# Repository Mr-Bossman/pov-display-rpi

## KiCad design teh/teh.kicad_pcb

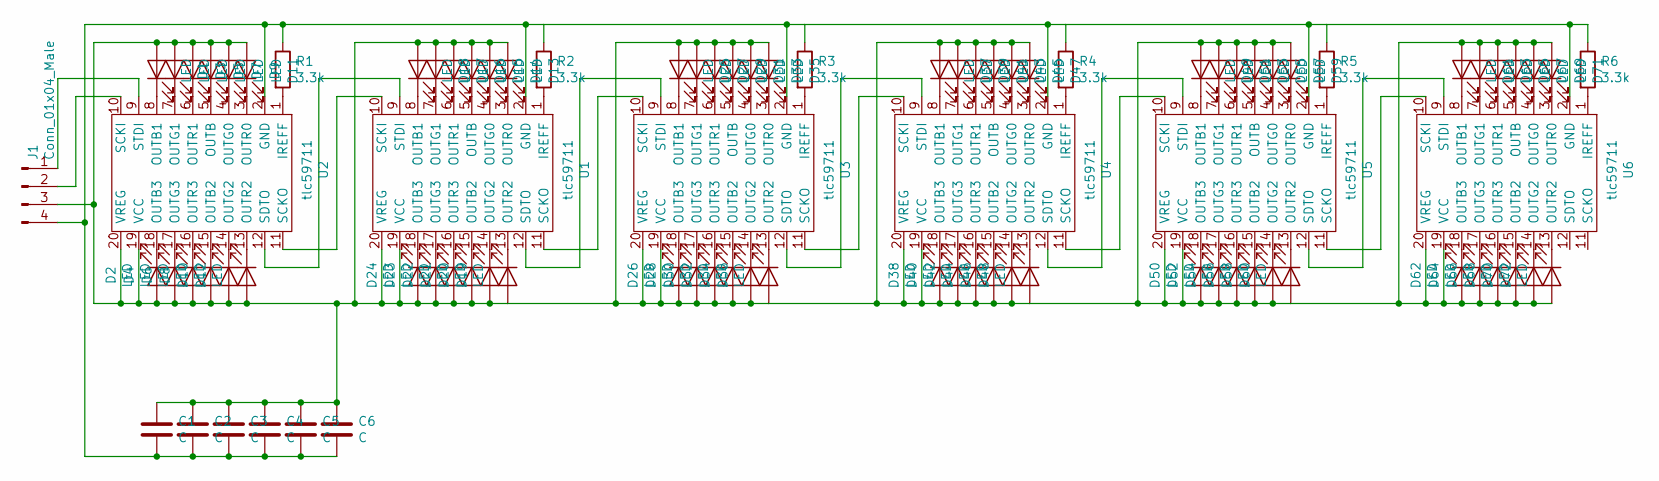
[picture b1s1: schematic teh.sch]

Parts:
C1, C2, C3, C4, C5, C6: C; C_0603_1608Metric
D1, D2, D3, D4, D5, D6, D7, D8, D9, D10, D11, D12, D13, D14, D15, D16, D17, D18, D19, D20, D21, D22, D23, D24, D25, D26, D27, D28, D29, D30, D31, D32, D33, D34, D35, D36, D37, D38, D39, D40, D41, D42, D43, D44, D45, D46, D47, D48, D49, D50, D51, D52, D53, D54, D55, D56, D57, D58, D59, D60, D61, D62, D63, D64, D65, D66, D67, D68, D69, D70, D71, D72: LED; LED_0603_1608Metric
J1: Conn_01x04_Male; PinSocket_1x04_P2.54mm_Vertical
R1, R2, R3, R4, R5, R6: 3.3k; R_0603_1608Metric
U1, U2, U3, U4, U5, U6: tlc59711; ETSSOP-20-1EP_4.4x6.5mm_P0.65mm_EP3x4.2mm_termal

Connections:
GND: C1.2, C2.2, C3.2, C4.2, C5.2, C6.2, J1.4, R1.1, R2.1, R3.1, R4.1, R5.1, R6.1, U1.2 (GND), U1.21 (GND), U2.2 (GND), U2.21 (GND), U3.2 (GND), U3.21 (GND), U4.2 (GND), U4.21 (GND), U5.2 (GND), U5.21 (GND), U6.2 (GND), U6.21 (GND)
unnamed: C1.1, C2.1, C3.1, C4.1, C5.1, C6.1, D1.2 (A), D2.2 (A), D3.2 (A), D4.2 (A), D5.2 (A), D6.2 (A), D7.2 (A), D8.2 (A), D9.2 (A), D10.2 (A), D11.2 (A), D12.2 (A), D13.2 (A), D14.2 (A), D15.2 (A), D16.2 (A), D17.2 (A), D18.2 (A), D19.2 (A), D20.2 (A), D21.2 (A), D22.2 (A), D23.2 (A), D24.2 (A), D25.2 (A), D26.2 (A), D27.2 (A), D28.2 (A), D29.2 (A), D30.2 (A), D31.2 (A), D32.2 (A), D33.2 (A), D34.2 (A), D35.2 (A), D36.2 (A), D37.2 (A), D38.2 (A), D39.2 (A), D40.2 (A), D41.2 (A), D42.2 (A), D43.2 (A), D44.2 (A), D45.2 (A), D46.2 (A), D47.2 (A), D48.2 (A), D49.2 (A), D50.2 (A), D51.2 (A), D52.2 (A), D53.2 (A), D54.2 (A), D55.2 (A), D56.2 (A), D57.2 (A), D58.2 (A), D59.2 (A), D60.2 (A), D61.2 (A), D62.2 (A), D63.2 (A), D64.2 (A), D65.2 (A), D66.2 (A), D67.2 (A), D68.2 (A), D69.2 (A), D70.2 (A), D71.2 (A), D72.2 (A), J1.3, U1.19 (VCC), U1.20 (VREG), U2.19 (VCC), U2.20 (VREG), U3.19 (VCC), U3.20 (VREG), U4.19 (VCC), U4.20 (VREG), U5.19 (VCC), U5.20 (VREG), U6.19 (VCC), U6.20 (VREG)
unnamed: D1.1 (K), U2.8 (OUTB1)
unnamed: D2.1 (K), U2.18 (OUTB3)
unnamed: D3.1 (K), U2.7 (OUTG1)
unnamed: D4.1 (K), U2.17 (OUTG3)
unnamed: D5.1 (K), U2.6 (OUTR1)
unnamed: D6.1 (K), U2.16 (OUTR3)
unnamed: D7.1 (K), U2.5 (OUTB)
unnamed: D8.1 (K), U2.15 (OUTB2)
unnamed: D9.1 (K), U2.4 (OUTG0)
unnamed: D10.1 (K), U2.14 (OUTG2)
unnamed: D11.1 (K), U2.3 (OUTR0)
unnamed: D12.1 (K), U2.13 (OUTR2)
unnamed: D13.1 (K), U1.3 (OUTR0)
unnamed: D14.1 (K), U1.4 (OUTG0)
unnamed: D15.1 (K), U1.5 (OUTB)
unnamed: D16.1 (K), U1.6 (OUTR1)
unnamed: D17.1 (K), U1.7 (OUTG1)
unnamed: D18.1 (K), U1.8 (OUTB1)
unnamed: D19.1 (K), U1.13 (OUTR2)
unnamed: D20.1 (K), U1.14 (OUTG2)
unnamed: D21.1 (K), U1.15 (OUTB2)
unnamed: D22.1 (K), U1.16 (OUTR3)
unnamed: D23.1 (K), U1.17 (OUTG3)
unnamed: D24.1 (K), U1.18 (OUTB3)
unnamed: D25.1 (K), U3.8 (OUTB1)
unnamed: D26.1 (K), U3.18 (OUTB3)
unnamed: D27.1 (K), U3.7 (OUTG1)
unnamed: D28.1 (K), U3.17 (OUTG3)
unnamed: D29.1 (K), U3.6 (OUTR1)
unnamed: D30.1 (K), U3.16 (OUTR3)
unnamed: D31.1 (K), U3.5 (OUTB)
unnamed: D32.1 (K), U3.15 (OUTB2)
unnamed: D33.1 (K), U3.4 (OUTG0)
unnamed: D34.1 (K), U3.14 (OUTG2)
unnamed: D35.1 (K), U3.3 (OUTR0)
unnamed: D36.1 (K), U3.13 (OUTR2)
unnamed: D37.1 (K), U4.8 (OUTB1)
unnamed: D38.1 (K), U4.18 (OUTB3)
unnamed: D39.1 (K), U4.7 (OUTG1)
unnamed: D40.1 (K), U4.17 (OUTG3)
unnamed: D41.1 (K), U4.6 (OUTR1)
unnamed: D42.1 (K), U4.16 (OUTR3)
unnamed: D43.1 (K), U4.5 (OUTB)
unnamed: D44.1 (K), U4.15 (OUTB2)
unnamed: D45.1 (K), U4.4 (OUTG0)
unnamed: D46.1 (K), U4.14 (OUTG2)
unnamed: D47.1 (K), U4.3 (OUTR0)
unnamed: D48.1 (K), U4.13 (OUTR2)
unnamed: D49.1 (K), U5.8 (OUTB1)
unnamed: D50.1 (K), U5.18 (OUTB3)
unnamed: D51.1 (K), U5.7 (OUTG1)
unnamed: D52.1 (K), U5.17 (OUTG3)
unnamed: D53.1 (K), U5.6 (OUTR1)
unnamed: D54.1 (K), U5.16 (OUTR3)
unnamed: D55.1 (K), U5.5 (OUTB)
unnamed: D56.1 (K), U5.15 (OUTB2)
unnamed: D57.1 (K), U5.4 (OUTG0)
unnamed: D58.1 (K), U5.14 (OUTG2)
unnamed: D59.1 (K), U5.3 (OUTR0)
unnamed: D60.1 (K), U5.13 (OUTR2)
unnamed: D61.1 (K), U6.8 (OUTB1)
unnamed: D62.1 (K), U6.18 (OUTB3)
unnamed: D63.1 (K), U6.7 (OUTG1)
unnamed: D64.1 (K), U6.17 (OUTG3)
unnamed: D65.1 (K), U6.6 (OUTR1)
unnamed: D66.1 (K), U6.16 (OUTR3)
unnamed: D67.1 (K), U6.5 (OUTB)
unnamed: D68.1 (K), U6.15 (OUTB2)
unnamed: D69.1 (K), U6.4 (OUTG0)
unnamed: D70.1 (K), U6.14 (OUTG2)
unnamed: D71.1 (K), U6.3 (OUTR0)
unnamed: D72.1 (K), U6.13 (OUTR2)
unnamed: J1.1, U2.9 (STDI)
unnamed: J1.2, U2.10 (SCKI)
unnamed: R1.2, U2.1 (IREFF)
unnamed: R2.2, U1.1 (IREFF)
unnamed: R3.2, U3.1 (IREFF)
unnamed: R4.2, U4.1 (IREFF)
unnamed: R5.2, U5.1 (IREFF)
unnamed: R6.2, U6.1 (IREFF)
unnamed: U1.9 (STDI), U2.12 (SDTO)
unnamed: U1.10 (SCKI), U2.11 (SCKO)
unnamed: U1.11 (SCKO), U3.10 (SCKI)
unnamed: U1.12 (SDTO), U3.9 (STDI)
unnamed: U3.11 (SCKO), U4.10 (SCKI)
unnamed: U3.12 (SDTO), U4.9 (STDI)
unnamed: U4.11 (SCKO), U5.10 (SCKI)
unnamed: U4.12 (SDTO), U5.9 (STDI)
unnamed: U5.11 (SCKO), U6.10 (SCKI)
unnamed: U5.12 (SDTO), U6.9 (STDI)

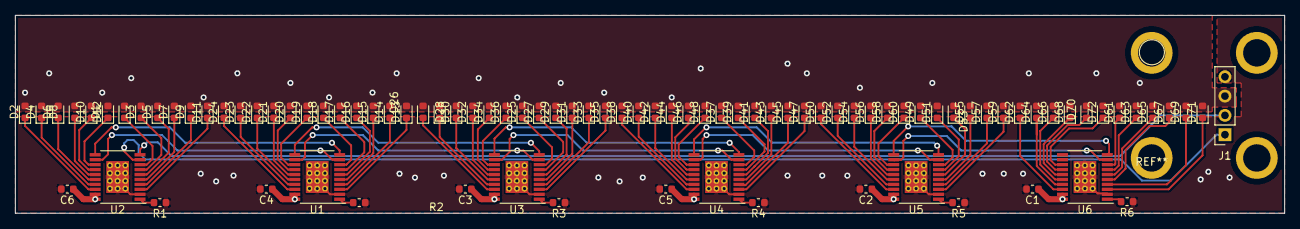
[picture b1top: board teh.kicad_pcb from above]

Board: 2 copper layers, 167.0 x 26.0 mm, 91 parts (0 on the bottom side), 92 nets.

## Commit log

2020-12-17 made make file and added spi demo from rpi website
2020-12-17 made the spi lib more library ish
2020-12-17 moveing to automake added main
2020-12-17 automake gets to compile
2020-12-17 get to compile but wont link dont know why added readme
2020-12-18 fixed errors and fromating
2020-12-21 added gpio non tested
2020-12-21 proceed with testing main program for sending data is working
2020-12-21 i need better way to get time, also forgot to close a file
2020-12-21 fixed typo
2020-12-21 forgot to send data not test code this took me 30 min bruh
2020-12-21 time should work now
2020-12-21 pin and time fixes
2020-12-21 changed to msb first for the driver and set spi speed to 12mhz
2020-12-21 hopefully faster gpio read
2020-12-21 fixed base addr and spilified code made gpio 0
2020-12-21 speed up its too slow :(
2020-12-21 multi threading make things faster
2020-12-21 ah yes arrays or threads jenk af
2020-12-21 fixed broken jenk but stil jenk this is hopefully just for testing
2020-12-21 i think i found th problem this is more debug
2020-12-21 should work now, we send all the data at once
2020-12-21 yeah boi it works now going to test image, slowed down spi, and make it work on 32 bit stupid pi
2020-12-21 try an image
2020-12-21 it works with a pre rendered image yaygit push!
2020-12-22 should still work made main into a display function
2020-12-22 forgot to add files
2020-12-22 test opencv
2020-12-22 should do video now
2020-12-22 oops forgot to save
2020-12-22 void to int
2020-12-22 should work now
2020-12-22 added fps thing
2020-12-22 forgot sothing in last commit
2020-12-22 try vsync, we need freesync
2020-12-22 lets try a buffer
2020-12-22 pretty code needs to be rotated 90* and needs some more functional fixing
2020-12-22 rotated 90* started making it more functional
2020-12-22 forgot to save some stuff
2020-12-22 works with 6 chips now, i did oops
2020-12-22 malloc slow
2020-12-22 bruh forgot to compile
2020-12-22 oops array indexing was off
2020-12-22 speed up
2020-12-22 hey it more works
2021-11-14 perf
2021-11-18 brightness corection add board
2021-12-10 works
2022-08-01 build better
2022-08-01 small fixes
2023-05-27 remove unused code and refactor a bit
2023-05-27 fix indentation
2023-05-27 split function for filling radial image buffer
2023-05-28 precompute_cartesian2polarLUT
2023-05-28 add simple test
2023-05-28 fix build
2023-05-29 add back openmp
2023-06-28 formating
2023-06-28 add fps
2024-03-07 move to using libgpiod
2024-03-07 makefile test
2024-03-07 stop when video done
2025-01-15 fix test
2025-01-15 fix nice val
